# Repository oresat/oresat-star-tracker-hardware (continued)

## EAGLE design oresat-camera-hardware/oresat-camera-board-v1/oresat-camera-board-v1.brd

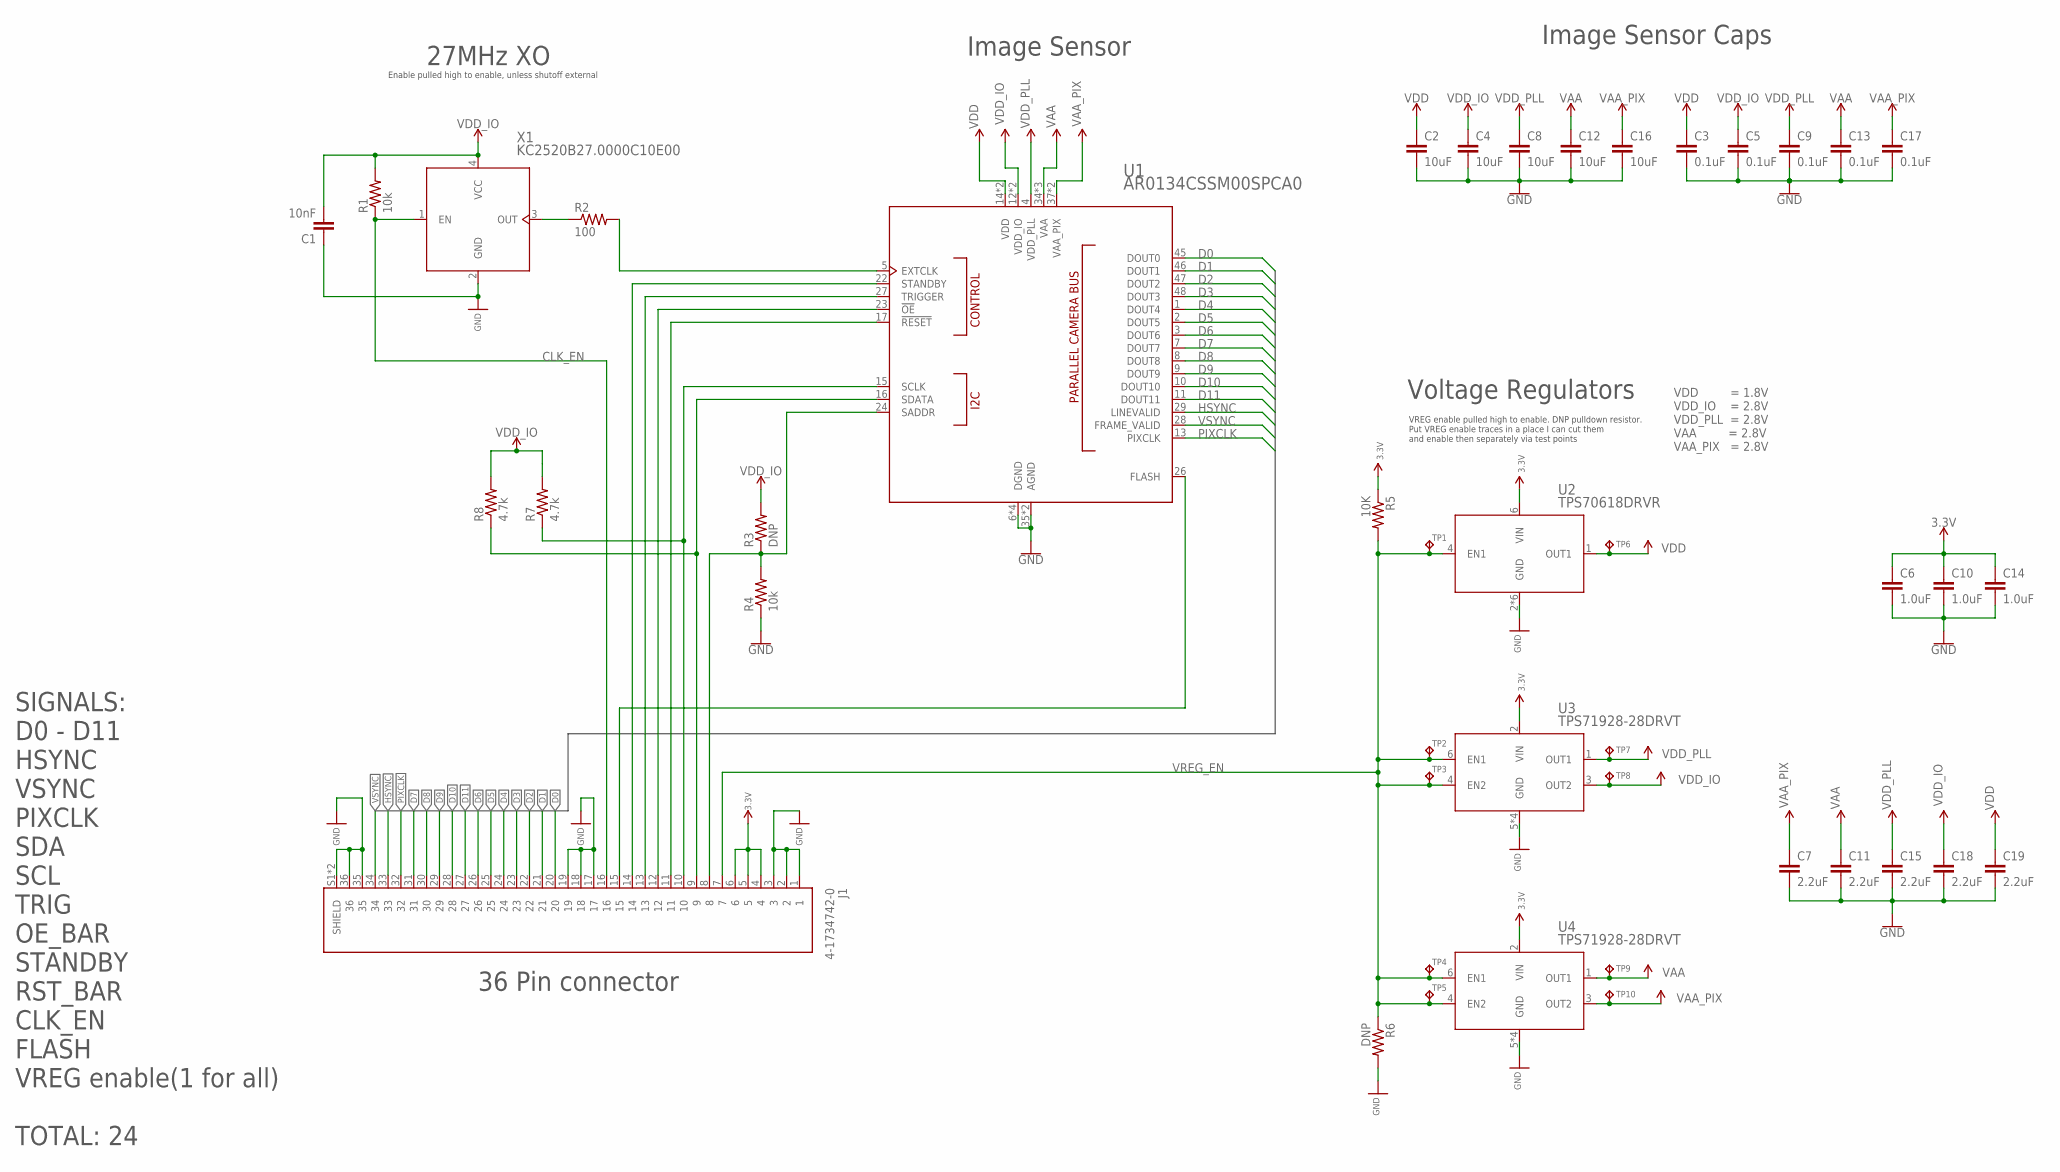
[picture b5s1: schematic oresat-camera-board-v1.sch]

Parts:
C1: 10nF; .0402-A-NOSILK
C2, C4, C8, C12, C16: 10uF; .0603-C-NOSILK
C3, C5, C9, C13, C17: 0.1uF; .0402-B-NOSILK
C6, C10, C14: 1.0uF; .0603-C-NOSILK
C7, C11, C15, C18, C19: 2.2uF; .0603-C-NOSILK
J1: 4-1734742-0; TE_4-1734742-0
R1, R4: 10k; .0402-B
R2: 100; .0402-B
R3, R6: DNP; .0402-B
R5: 10K; .0402-B
R7, R8: 4.7k; .0402-B
TP1, TP2, TP3, TP4, TP5, TP6, TP7, TP8, TP9, TP10: TPTP06R; TP06R
U1: AR0134CSSM00SPCA0
U2: TPS70618DRVR; DRV6_1P6X1
U3, U4: TPS71928-28DRVT; DRV6_1P6X1
X1: KC2520B27.0000C10E00; OSC_KYOCERA_KC2520B

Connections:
3.3V: C6.1, C10.1, C14.1, J1.4, J1.5, J1.6, R5.1, U2.6 (VIN), U3.2 (VIN), U4.2 (VIN)
CLK_EN: J1.16, R1.1, X1.1 (EN)
D0: J1.20, U1.45 (DOUT0)
D1: J1.21, U1.46 (DOUT1)
D2: J1.22, U1.47 (DOUT2)
D3: J1.23, U1.48 (DOUT3)
D4: J1.24, U1.1 (DOUT4)
D5: J1.25, U1.2 (DOUT5)
D6: J1.26, U1.3 (DOUT6)
D7: J1.31, U1.7 (DOUT7)
D8: J1.30, U1.8 (DOUT8)
D9: J1.29, U1.9 (DOUT9)
D10: J1.28, U1.10 (DOUT10)
D11: J1.27, U1.11 (DOUT11)
GND: C1.1, C2.2, C3.2, C4.2, C5.2, C6.2, C7.2, C8.2, C9.2, C10.2, C11.2, C12.2, C13.2, C14.2, C15.2, C16.2, C17.2, C18.2, C19.2, J1.1, J1.2, J1.3, J1.17, J1.18, J1.19, J1.35, J1.36, J1.S1 (SHIELD), J1.S2 (SHIELD), R4.1, R6.2, U1.6 (DGND), U1.25 (DGND), U1.30 (DGND), U1.35 (AGND), U1.39 (AGND), U1.44 (DGND), U2.2 (GND), U2.3 (GND), U2.5 (GND), U2.7 (GND), U2.8 (GND), U2.9 (GND), U3.5 (GND), U3.7 (GND), U3.8 (GND), U3.9 (GND), U4.5 (GND), U4.7 (GND), U4.8 (GND), U4.9 (GND), X1.2 (GND)
HSYNC: J1.33, U1.29 (LINEVALID)
unnamed: R2.1, X1.3 (OUT)
unnamed: R2.2, U1.5 (EXTCLK)
unnamed: J1.9, R8.1, U1.16 (SDATA)
unnamed: J1.10, R7.1, U1.15 (SCLK)
unnamed: J1.8, R3.1, R4.2, U1.24 (SADDR)
unnamed: J1.11, U1.17 (!RESET)
unnamed: J1.12, U1.23 (!OE)
unnamed: J1.13, U1.27 (TRIGGER)
unnamed: J1.14, U1.22 (STANDBY)
unnamed: J1.15, U1.26 (FLASH)
PIXCLK: J1.32, U1.13 (PIXCLK)
VAA: C11.1, C12.1, C13.1, TP9.TP, U1.34 (VAA), U1.36 (VAA), U1.40 (VAA), U4.1 (OUT1)
VAA_PIX: C7.1, C16.1, C17.1, TP10.TP, U1.37 (VAA_PIX), U1.38 (VAA_PIX), U4.3 (OUT2)
VDD: C2.1, C3.1, C19.1, TP6.TP, U1.14 (VDD), U1.19 (VDD), U2.1 (OUT1)
VDD_IO: C1.2, C4.1, C5.1, C18.1, R1.2, R3.2, R7.2, R8.2, TP8.TP, U1.12 (VDD_IO), U1.18 (VDD_IO), U3.3 (OUT2), X1.4 (VCC)
VDD_PLL: C8.1, C9.1, C15.1, TP7.TP, U1.4 (VDD_PLL), U3.1 (OUT1)
VREG_EN: J1.7, R5.2, R6.1, TP1.TP, TP2.TP, TP3.TP, TP4.TP, TP5.TP, U2.4 (EN1), U3.4 (EN2), U3.6 (EN1), U4.4 (EN2), U4.6 (EN1)
VSYNC: J1.34, U1.28 (FRAME_VALID)

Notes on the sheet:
Voltage Regulators
Image Sensor
27MHz XO
SIGNALS: D0 - D11 HSYNC VSYNC PIXCLK SDA SCL TRIG OE_BAR STANDBY RST_BAR CLK_EN FLASH VREG enable(1 for all) TOTAL: 24
VREG enable pulled high to enable. DNP pulldown resistor. Put VREG enable traces in a place I can cut them and enable then separately via test points
Enable pulled high to enable, unless shutoff external
VDD = 1.8V VDD_IO = 2.8V VDD_PLL = 2.8V VAA = 2.8V VAA_PIX = 2.8V
Image Sensor Caps
36 Pin connector

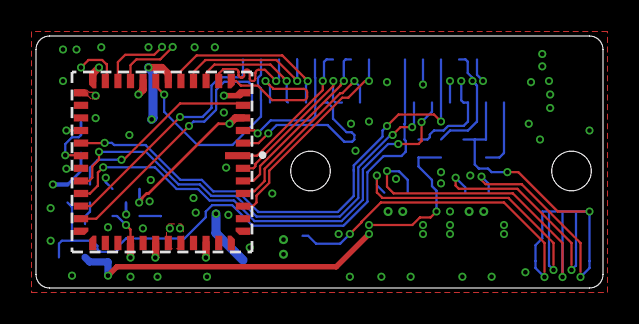
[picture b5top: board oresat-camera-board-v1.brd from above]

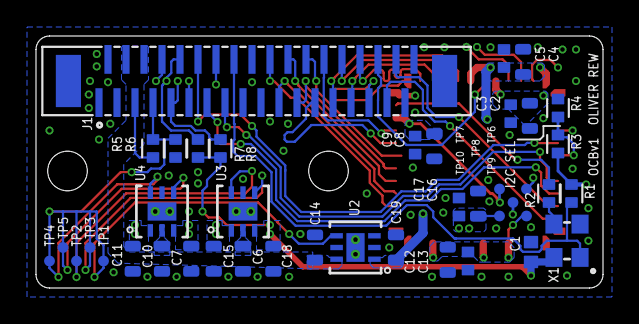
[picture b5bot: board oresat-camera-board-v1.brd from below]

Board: 4 copper layers, 31.5 x 14.0 mm, 43 parts (42 on the bottom side), 34 nets.

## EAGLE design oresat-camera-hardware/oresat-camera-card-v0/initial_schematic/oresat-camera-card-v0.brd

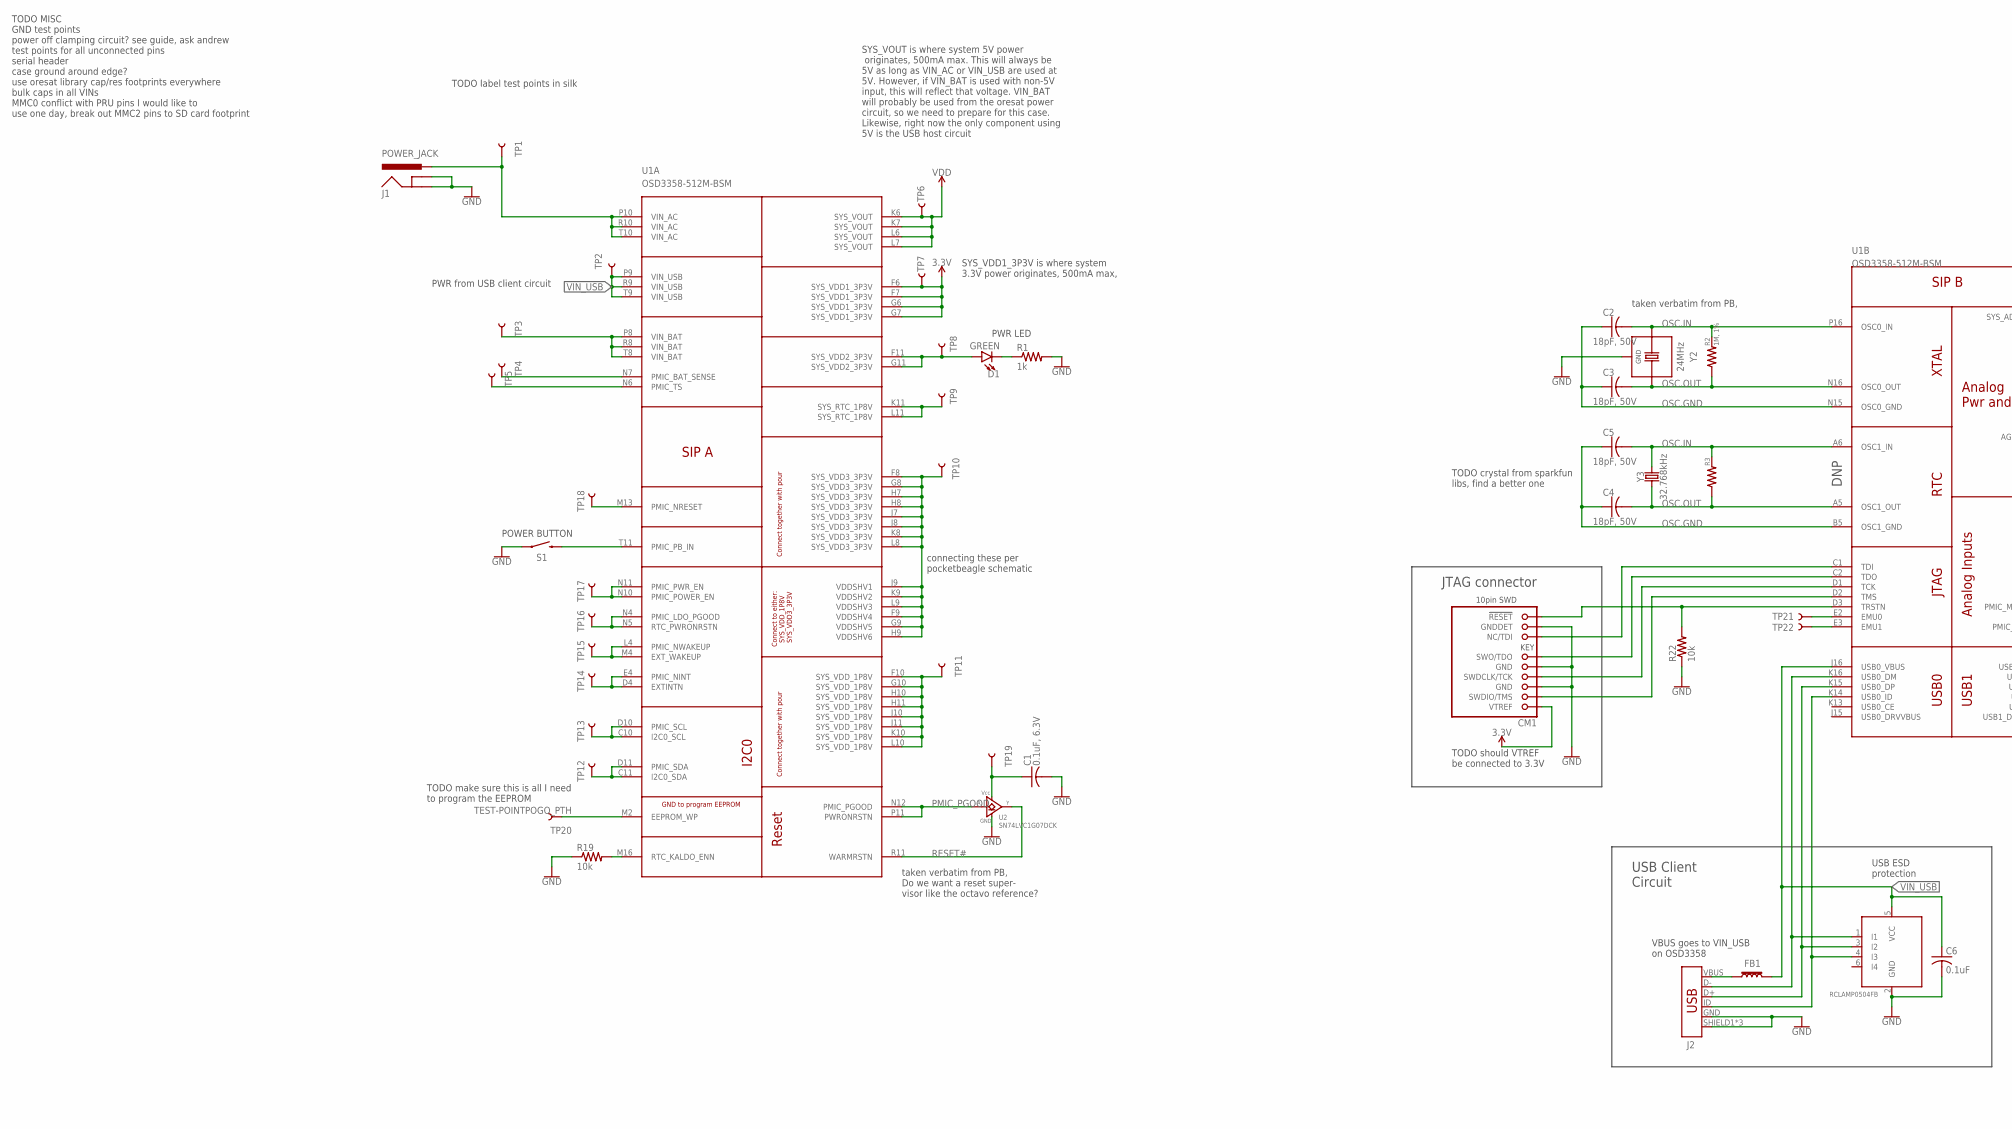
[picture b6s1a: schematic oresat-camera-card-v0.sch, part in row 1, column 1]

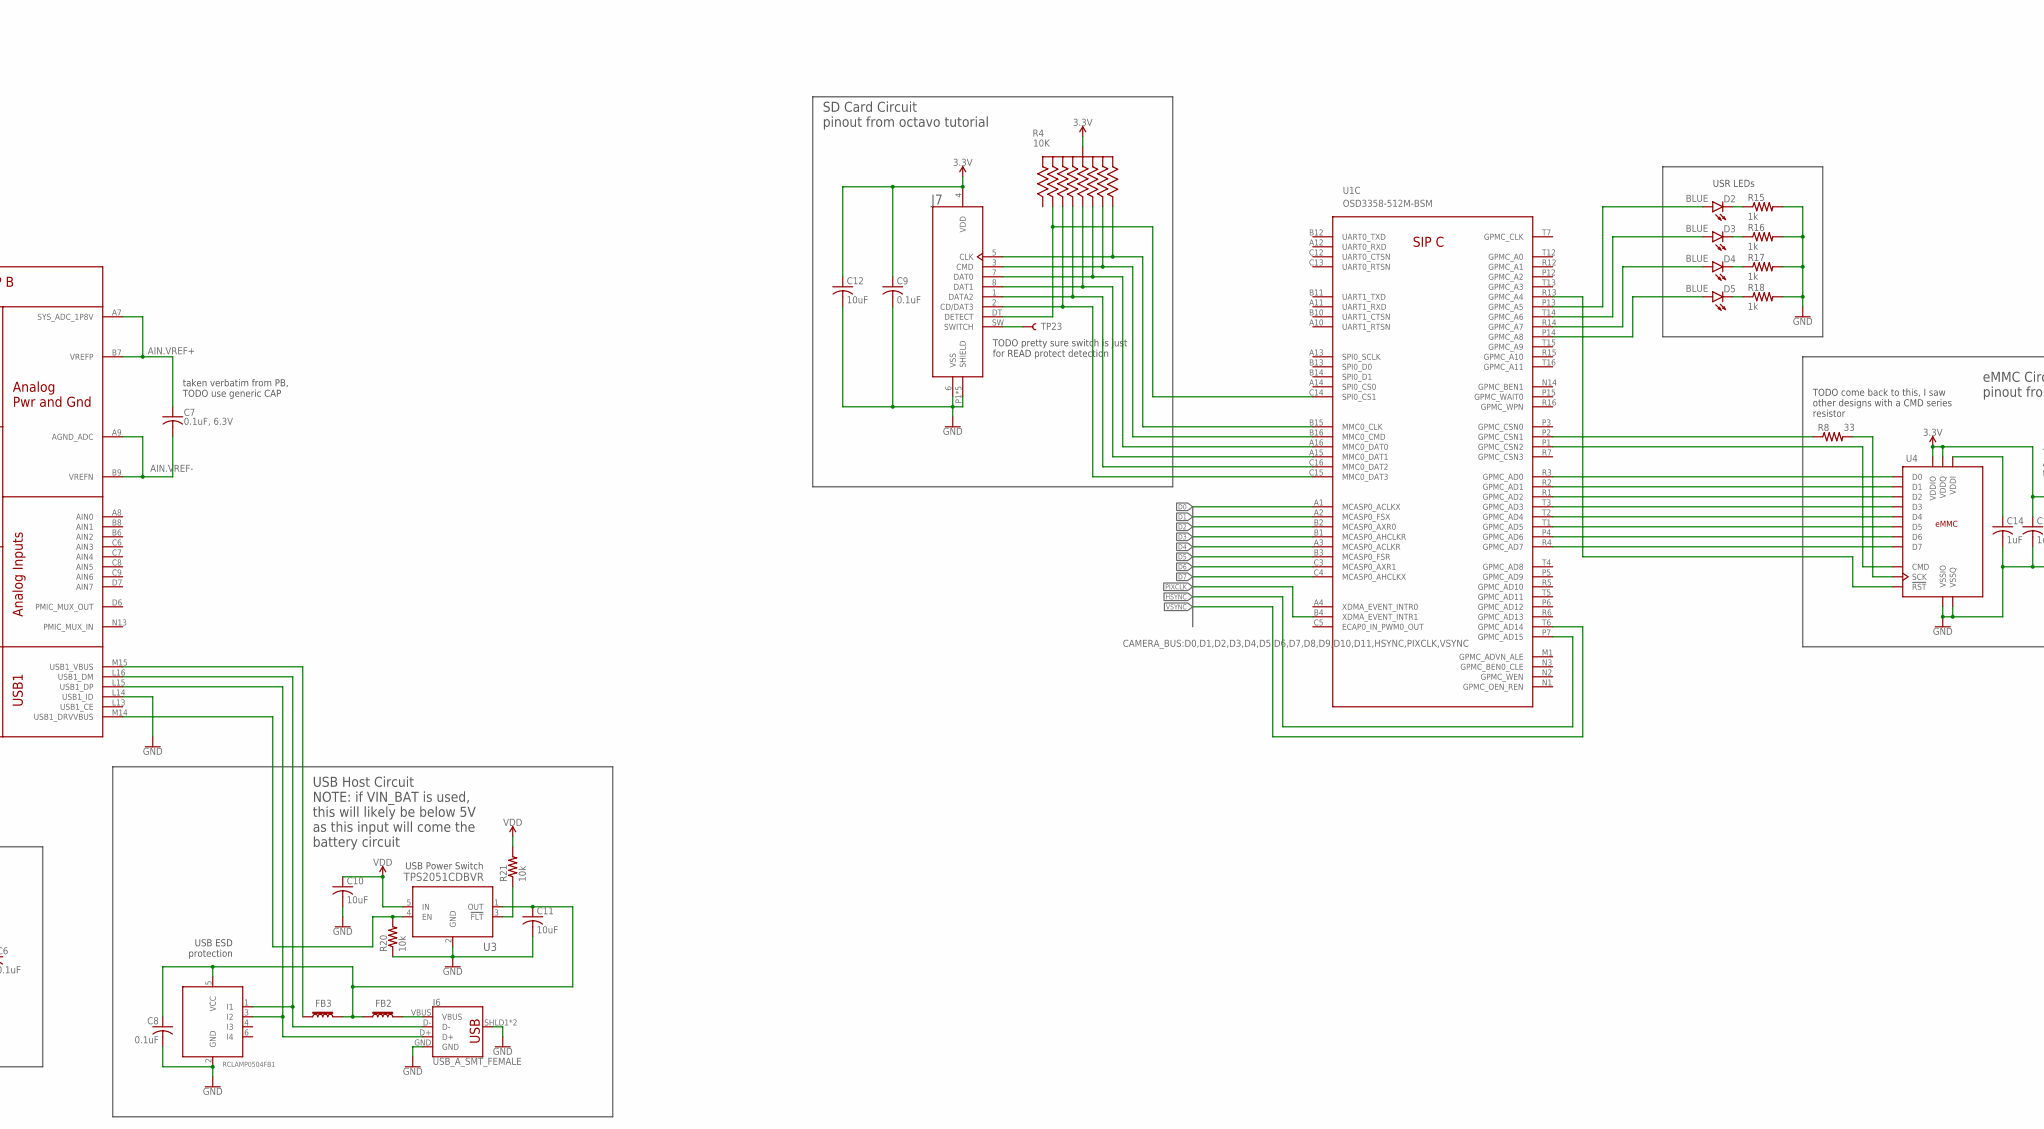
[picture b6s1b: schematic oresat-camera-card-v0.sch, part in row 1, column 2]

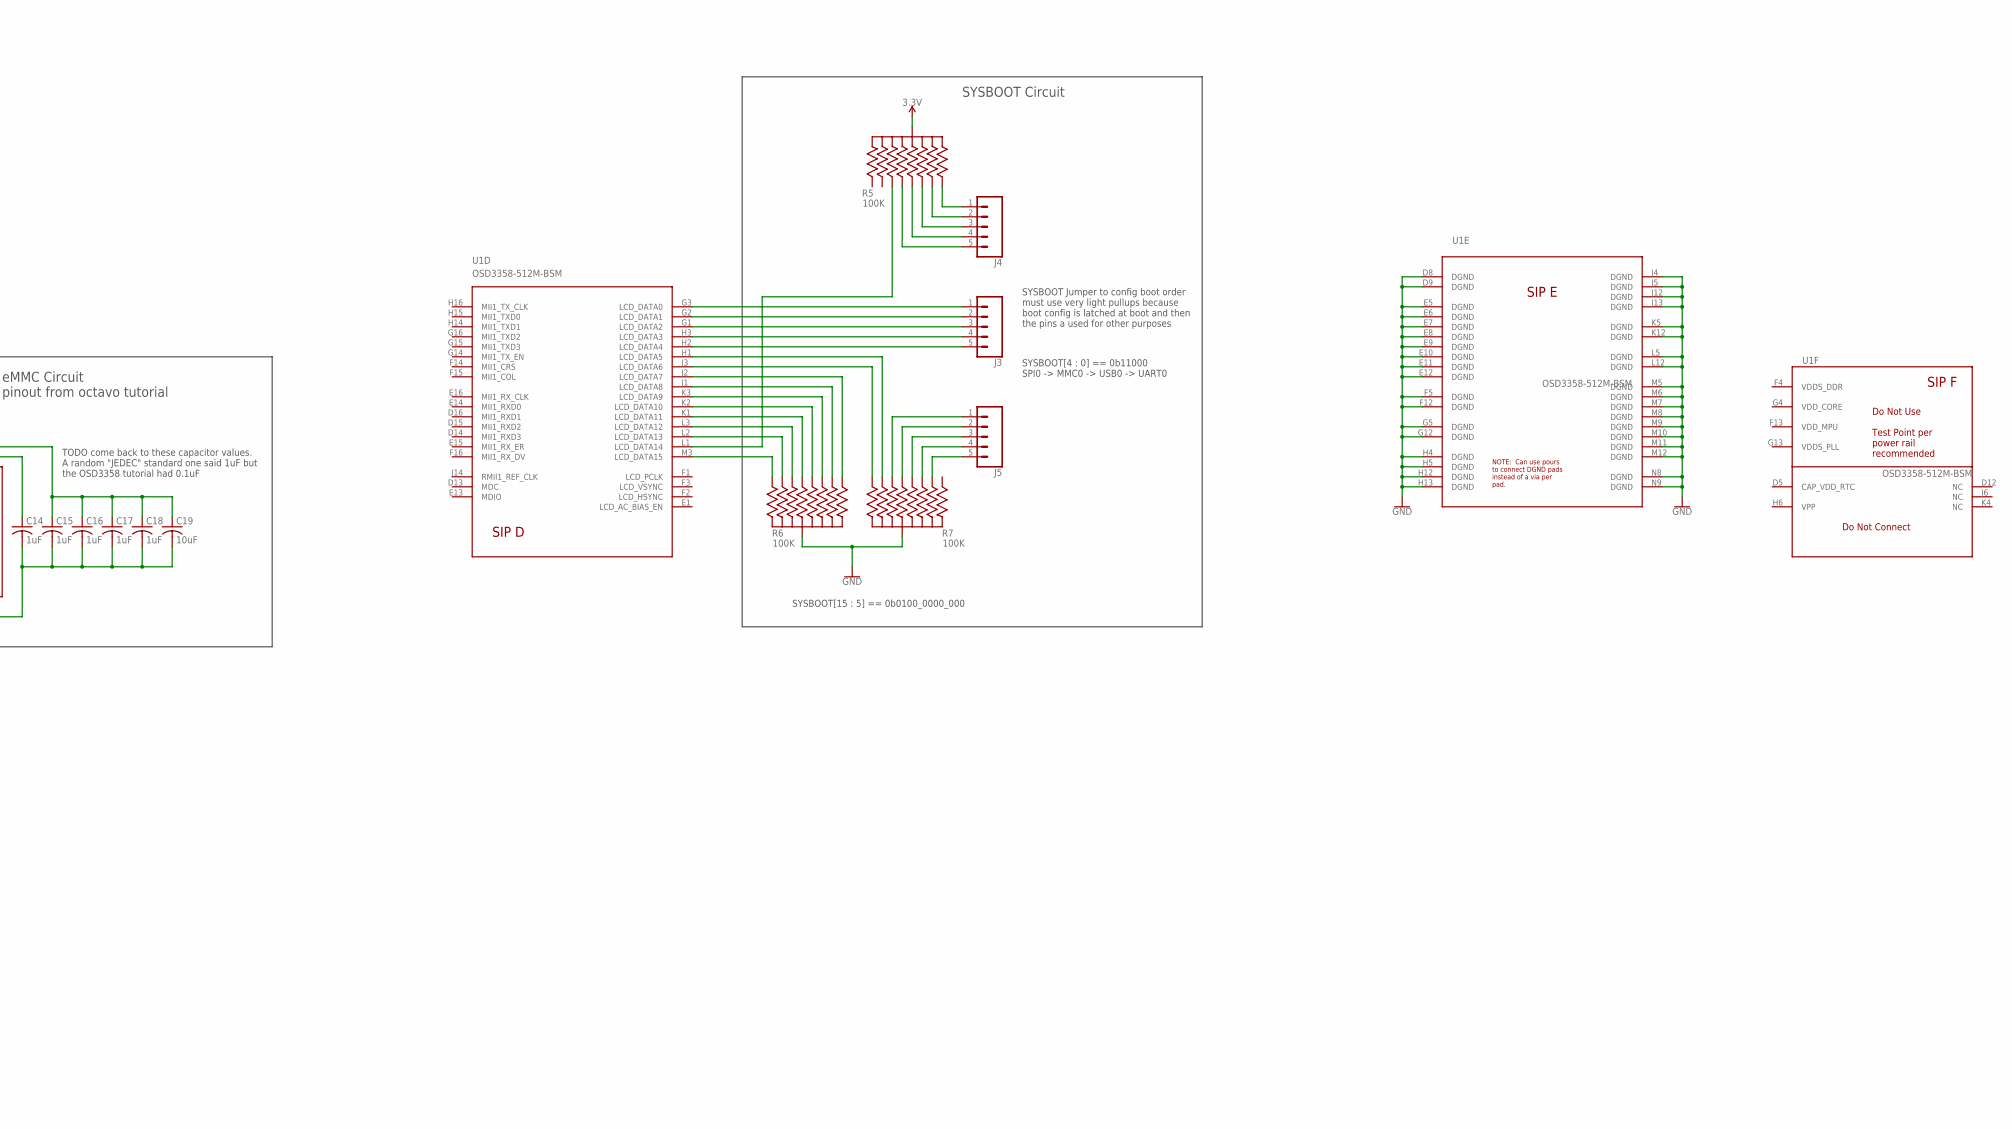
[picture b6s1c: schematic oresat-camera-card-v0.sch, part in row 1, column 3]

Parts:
C1, C7: 0.1uF, 6.3V; C0603
C2, C3, C4, C5: 18pF, 50V; C0603
C6, C8, C9: 0.1uF; C0603
C10, C11, C12, C19: 10uF; C0603
C14, C15, C16, C17, C18: 1uF; C0603
CM1: FTSH-105-XX-X-DV-K; CON10_2X5_DUK_FTSH
D1: GREEN; LED-0603
D2, D3, D4, D5: BLUE; LED-0603
FB1, FB2, FB3: 30Ω/1.8A; 0603
J1: POWER_JACK; POWER_JACK_PTH
J2: USB_MICRO-B_FEMALE-SMT; USB-B-MICRO-SMD
J3, J4, J5: CONN_05; 1X05
J6: USB_A_SMT_FEMALE; USB-A-S-SILK-FEMALE
J7: 503182-1852; MOLEX_503182-1852
R1, R15, R16, R17, R18: 1k; .0603-A
R2, R3: 1M, 1%; .0603-A
R4: 10K; ARRAY_EXBA-M
R5, R6, R7: 100K; ARRAY_EXBA-M
R8: 33; .0603-A
R19, R20, R21, R22: 10k; .0603-A
RCLAMP0504FB, RCLAMP0504FB1: RCLAMP0504FB; SC70-6
S1: MOMENTARY-SWITCH-SPST-SMD-4.6X2.8MM; TACTILE_SWITCH_SMD_4.6X2.8MM
TP1, TP2, TP3, TP4, TP5, TP6, TP7, TP8, TP9, TP10, TP11, TP12, TP13, TP14, TP15, TP16, TP17, TP18, TP19, TP21, TP22, TP23: TEST-POINT3X4; PAD.03X.04
TP20: TEST-POINTPOGO_PTH; 1X01_NO_SILK
U1: OSD3358-512M-BSM; OSD335X-BGA-256
U2: SN74LVC1G07DCK; SC70(TI-DCK)
U3: TPS2051CDBVR; DBV5
U4: EMMC+RESET-BA; BGA-153(11.5X13)(EMMC-BA)
Y2: 24MHz; 5X3.2-4SMD
Y3: 32.768kHz; CRYSTAL-SMD-3.2X1.5MM

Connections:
3.3V: C9.1, C12.1, C15.1, C16.1, C17.1, C18.1, C19.1, CM1.1 (VTREF), J7.4 (VDD), R4.5 (55), R4.10 (55), R5.5 (55), R5.10 (55), TP7.P$1, U1.F6 (SYS_VDD1_3P3V), U1.F7 (SYS_VDD1_3P3V), U1.G6 (SYS_VDD1_3P3V), U1.G7 (SYS_VDD1_3P3V), U4.C6 (VDDQ), U4.E6 (VDDIO), U4.F5 (VDDIO), U4.J10 (VDDIO), U4.K9 (VDDIO), U4.M4 (VDDQ), U4.N4 (VDDQ), U4.P3 (VDDQ), U4.P5 (VDDQ)
5V: C10.1, R21.2, TP6.P$1, U1.K6 (SYS_VOUT), U1.K7 (SYS_VOUT), U1.L6 (SYS_VOUT), U1.L7 (SYS_VOUT), U3.5 (IN)
AIN.VREF+: C7.1, U1.A7 (SYS_ADC_1P8V), U1.B7 (VREFP)
AIN.VREF-: C7.2, U1.A9 (AGND_ADC), U1.B9 (VREFN)
D0: U1.A1 (MCASP0_ACLKX)
D1: U1.A2 (MCASP0_FSX)
D2: U1.B2 (MCASP0_AXR0)
D3: U1.B1 (MCASP0_AHCLKR)
D4: U1.A3 (MCASP0_ACLKR)
D5: U1.B3 (MCASP0_FSR)
D6: U1.C3 (MCASP0_AXR1)
D7: U1.C4 (MCASP0_AHCLKX)
GND: C1.2, C6.2, C8.2, C9.2, C10.2, C11.2, C12.2, C14.2, C15.2, C16.2, C17.2, C18.2, C19.2, CM1.3 (GND), CM1.5 (GND), CM1.9 (GNDDET), J1.GND, J1.GNDBREAK, J2.GND, J2.SHIELD1 (SHIELD), J2.SHIELD2 (SHIELD), J2.SHIELD3 (SHIELD), J6.GND, J6.SHLD1 (SHIELD), J6.SHLD2 (SHIELD), J7.6 (VSS), J7.P1 (SHIELD), J7.P2 (SHIELD), J7.P3 (SHIELD), J7.P4 (SHIELD), J7.P5 (SHIELD), R1.2, R6.5 (55), R6.10 (55), R7.5 (55), R7.10 (55), R15.2, R16.2, R17.2, R18.2, R19.1, R20.1, R22.1, RCLAMP0504FB.2 (GND), RCLAMP0504FB1.2 (GND), S1.1, S1.2 (1), U1.D8 (DGND), U1.D9 (DGND), U1.E5 (DGND), U1.E6 (DGND), U1.E7 (DGND), U1.E8 (DGND), U1.E9 (DGND), U1.E10 (DGND), U1.E11 (DGND), U1.E12 (DGND), U1.F5 (DGND), U1.F12 (DGND), U1.G5 (DGND), U1.G12 (DGND), U1.H4 (DGND), U1.H5 (DGND), U1.H12 (DGND), U1.H13 (DGND), U1.J4 (DGND), U1.J5 (DGND), U1.J12 (DGND), U1.J13 (DGND), U1.K5 (DGND), U1.K12 (DGND), U1.L5 (DGND), U1.L12 (DGND), U1.L14 (USB1_ID), U1.M5 (DGND), U1.M6 (DGND), U1.M7 (DGND), U1.M8 (DGND), U1.M9 (DGND), U1.M10 (DGND), U1.M11 (DGND), U1.M12 (DGND), U1.N8 (DGND), U1.N9 (DGND), U2.3 (GND), U3.2 (GND), U4.C4 (VSSQ), U4.E7 (VSSIO), U4.G5 (VSSIO), U4.H10 (VSSIO), U4.K8 (VSSIO), U4.N2 (VSSQ), U4.N5 (VSSQ), U4.P4 (VSSQ), U4.P6 (VSSQ), Y2.2 (GND), Y2.4 (GND)
HSYNC: U1.P7 (GPMC_AD15)
unnamed: J1.PWR, TP1.P$1, U1.P10 (VIN_AC), U1.R10 (VIN_AC), U1.T10 (VIN_AC)
unnamed: FB1.1, J2.VBUS
unnamed: TP3.P$1, U1.P8 (VIN_BAT), U1.R8 (VIN_BAT), U1.T8 (VIN_BAT)
unnamed: D1.A, TP8.P$1, U1.F11 (SYS_VDD2_3P3V), U1.G11 (SYS_VDD2_3P3V)
unnamed: TP4.P$1, U1.N7 (PMIC_BAT_SENSE)
unnamed: TP5.P$1, U1.N6 (PMIC_TS)
unnamed: TP9.P$1, U1.K11 (SYS_RTC_1P8V), U1.L11 (SYS_RTC_1P8V)
unnamed: TP11.P$1, U1.F10 (SYS_VDD_1P8V), U1.G10 (SYS_VDD_1P8V), U1.H10 (SYS_VDD_1P8V), U1.H11 (SYS_VDD_1P8V), U1.J10 (SYS_VDD_1P8V), U1.J11 (SYS_VDD_1P8V), U1.K10 (SYS_VDD_1P8V), U1.L10 (SYS_VDD_1P8V)
unnamed: TP12.P$1, U1.C11 (I2C0_SDA), U1.D11 (PMIC_SDA)
unnamed: TP10.P$1, U1.F8 (SYS_VDD3_3P3V), U1.F9 (VDDSHV4), U1.G8 (SYS_VDD3_3P3V), U1.G9 (VDDSHV5), U1.H7 (SYS_VDD3_3P3V), U1.H8 (SYS_VDD3_3P3V), U1.H9 (VDDSHV6), U1.J7 (SYS_VDD3_3P3V), U1.J8 (SYS_VDD3_3P3V), U1.J9 (VDDSHV1), U1.K8 (SYS_VDD3_3P3V), U1.K9 (VDDSHV2), U1.L8 (SYS_VDD3_3P3V), U1.L9 (VDDSHV3)
unnamed: D1.C, R1.1
unnamed: TP13.P$1, U1.C10 (I2C0_SCL), U1.D10 (PMIC_SCL)
unnamed: TP14.P$1, U1.D4 (EXTINTN), U1.E4 (PMIC_NINT)
unnamed: TP15.P$1, U1.L4 (PMIC_NWAKEUP), U1.M4 (EXT_WAKEUP)
unnamed: TP16.P$1, U1.N4 (PMIC_LDO_PGOOD), U1.N5 (RTC_PWRONRSTN)
unnamed: TP17.P$1, U1.N10 (PMIC_POWER_EN), U1.N11 (PMIC_PWR_EN)
unnamed: S1.3 (2), S1.4 (2), U1.T11 (PMIC_PB_IN)
unnamed: TP18.P$1, U1.M13 (PMIC_NRESET)
unnamed: CM1.8 (NC/TDI), U1.C1 (TDI)
unnamed: CM1.6 (SWO/TDO), U1.C2 (TDO)
unnamed: CM1.4 (SWDCLK/TCK), U1.D1 (TCK)
unnamed: CM1.2 (SWDIO/TMS), U1.D2 (TMS)
unnamed: J7.5 (CLK), R4.6 (66), U1.B15 (MMC0_CLK)
unnamed: J3.1, U1.G3 (LCD_DATA0)
unnamed: J3.2, U1.G2 (LCD_DATA1)
unnamed: J3.3, U1.G1 (LCD_DATA2)
unnamed: J3.4, U1.H3 (LCD_DATA3)
unnamed: J3.5, U1.H2 (LCD_DATA4)
unnamed: R7.4 (44), U1.H1 (LCD_DATA5)
unnamed: R7.6 (66), U1.J3 (LCD_DATA6)
unnamed: R6.1 (11), U1.J2 (LCD_DATA7)
unnamed: R6.9 (99), U1.J1 (LCD_DATA8)
unnamed: R6.2 (22), U1.K3 (LCD_DATA9)
unnamed: R6.8 (88), U1.K2 (LCD_DATA10)
unnamed: R6.3 (33), U1.K1 (LCD_DATA11)
unnamed: R6.7 (77), U1.L3 (LCD_DATA12)
unnamed: R6.4 (44), U1.L2 (LCD_DATA13)
unnamed: R5.2 (22), U1.L1 (LCD_DATA14)
unnamed: R6.6 (66), U1.M3 (LCD_DATA15)
unnamed: D2.C, R15.1
unnamed: D3.C, R16.1
unnamed: D4.C, R17.1
unnamed: D5.C, R18.1
unnamed: D2.A, U1.P13 (GPMC_A5)
unnamed: D3.A, U1.T14 (GPMC_A6)
unnamed: D4.A, U1.R14 (GPMC_A7)
unnamed: D5.A, U1.P14 (GPMC_A8)
unnamed: R19.2, U1.M16 (RTC_KALDO_ENN)
unnamed: TP20.1, U1.M2 (EEPROM_WP)
unnamed: J2.D-, RCLAMP0504FB.1 (I1), U1.K16 (USB0_DM)
unnamed: J2.D+, RCLAMP0504FB.3 (I2), U1.K15 (USB0_DP)
unnamed: J2.ID, RCLAMP0504FB.4 (I3), U1.K14 (USB0_ID)
unnamed: R20.2, U1.M14 (USB1_DRVVBUS), U3.4 (EN)
unnamed: FB2.2, J6.VBUS
unnamed: R21.1, U3.3 (!FLT)
unnamed: FB3.1, U1.M15 (USB1_VBUS)
unnamed: J6.D-, RCLAMP0504FB1.1 (I1), U1.L16 (USB1_DM)
unnamed: J6.D+, RCLAMP0504FB1.3 (I2), U1.L15 (USB1_DP)
unnamed: TP22.P$1, U1.E3 (EMU1)
unnamed: J7.3 (CMD), R4.4 (44), U1.B16 (MMC0_CMD)
unnamed: J7.7 (DAT0), R4.7 (77), U1.A16 (MMC0_DAT0)
unnamed: J7.8 (DAT1), R4.3 (33), U1.A15 (MMC0_DAT1)
unnamed: J7.1 (DATA2), R4.8 (88), U1.C16 (MMC0_DAT2)
unnamed: J7.2 (CD/DAT3), R4.2 (22), U1.C15 (MMC0_DAT3)
unnamed: J7.DT (DETECT), R4.9 (99), U1.C14 (SPI0_CS1)
unnamed: J5.1, R7.7 (77)
unnamed: J5.2, R7.3 (33)
unnamed: J5.3, R7.8 (88)
unnamed: J5.4, R7.2 (22)
unnamed: J5.5, R7.9 (99)
unnamed: J4.1, R5.6 (66)
unnamed: J4.2, R5.4 (44)
unnamed: J4.3, R5.7 (77)
unnamed: J4.4, R5.3 (33)
unnamed: J4.5, R5.8 (88)
unnamed: C14.1, U4.C2 (VDDI)
unnamed: U1.R3 (GPMC_AD0), U4.A3 (D0)
unnamed: U1.R2 (GPMC_AD1), U4.A4 (D1)
unnamed: U1.R1 (GPMC_AD2), U4.A5 (D2)
unnamed: U1.T3 (GPMC_AD3), U4.B2 (D3)
unnamed: U1.T2 (GPMC_AD4), U4.B3 (D4)
unnamed: U1.T1 (GPMC_AD5), U4.B4 (D5)
unnamed: U1.P4 (GPMC_AD6), U4.B5 (D6)
unnamed: U1.R4 (GPMC_AD7), U4.B6 (D7)
unnamed: U1.P1 (GPMC_CSN2), U4.M5 (CMD)
unnamed: R8.1, U1.P2 (GPMC_CSN1)
unnamed: R8.2, U4.M6 (SCK)
unnamed: U1.R13 (GPMC_A4), U4.K5 (!RST!)
unnamed: CM1.10 (!RESET), R22.2, U1.D3 (TRSTN)
unnamed: TP21.P$1, U1.E2 (EMU0)
unnamed: J7.SW (SWITCH), TP23.P$1
OSC.GND: C2.1, C3.1, C4.1, C5.1, U1.B5 (OSC1_GND), U1.N15 (OSC0_GND)
OSC.IN: C2.2, C5.2, R2.2, R3.2, U1.A6 (OSC1_IN), U1.P16 (OSC0_IN), Y2.1 (X1), Y3.P$2 (2)
OSC.OUT: C3.2, C4.2, R2.1, R3.1, U1.A5 (OSC1_OUT), U1.N16 (OSC0_OUT), Y2.3 (X2), Y3.P$1 (1)
PIXCLK: U1.B4 (XDMA_EVENT_INTR1)
PMIC_PGOOD: U1.N12 (PMIC_PGOOD), U1.P11 (PWRONRSTN), U2.2 (A)
RESET#: U1.R11 (WARMRSTN), U2.4 (Y)
VDD_RTC: C1.1, TP19.P$1, U2.5 (VCC)
VIN_USB: C6.1, C8.1, C11.1, FB1.2, FB2.1, FB3.2, RCLAMP0504FB.5 (VCC), RCLAMP0504FB1.5 (VCC), TP2.P$1, U1.J16 (USB0_VBUS), U1.P9 (VIN_USB), U1.R9 (VIN_USB), U1.T9 (VIN_USB), U3.1 (OUT)
VSYNC: U1.T6 (GPMC_AD14)

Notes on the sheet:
TODO label test points in silk
SYS_VOUT is where system 5V power originates, 500mA max. This will always be 5V as long as VIN_AC or VIN_USB are used at 5V. However, if VIN_BAT is used with non-5V input, this will reflect that voltage. VIN_BAT will probably be used from the oresat power circuit, so we need to prepare for this cas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
SYS_VDD1_3P3V is where system 3.3V power originates, 500mA max,
connecting these per pocketbeagle schematic
TODO MISC GND test points power off clamping circuit? see guide, ask andrew test points for all unconnected pins serial header case ground around edge? use oresat library cap/res footprints everywhere bulk caps in all VINs MMC0 conflict with PRU pins I would like to use one day, break out MMC2 pins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
taken verbatim from PB, TODO use generic CAP
POWER BUTTON
PWR LED
taken verbatim from PB, Do we want a reset super- visor like the octavo reference?
taken verbatim from PB,
DNP
TODO crystal from sparkfun libs, find a better one
TODO should VTREF be connected to 3.3V
SYSBOOT Jumper to config boot order must use very light pullups because boot config is latched at boot and then the pins a used for other purposes
SYSBOOT[15 : 5] == 0b0100_0000_000
SYSBOOT[4 : 0] == 0b11000 SPI0 -> MMC0 -> USB0 -> UART0
USR LEDs
TODO make sure this is all I need to program the EEPROM
VBUS goes to VIN_USB on OSD3358
PWR from USB client circuit
USB ESD protection
USB Host Circuit NOTE: if VIN_BAT is used, this will likely be below 5V as this input will come the battery circuit
USB Power Switch
JTAG connector
USB Client Circuit
TODO come back to these capacitor values. A random "JEDEC" standard one said 1uF but the OSD3358 tutorial had 0.1uF
TODO come back to this, I saw other designs with a CMD series resistor
eMMC Circuit pinout from octavo tutorial
SD Card Circuit pinout from octavo tutorial
TODO pretty sure switch is just for READ protect detection
SYSBOOT Circuit

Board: 4 copper layers, 82 parts (0 on the bottom side), 103 nets, no tracks yet.
